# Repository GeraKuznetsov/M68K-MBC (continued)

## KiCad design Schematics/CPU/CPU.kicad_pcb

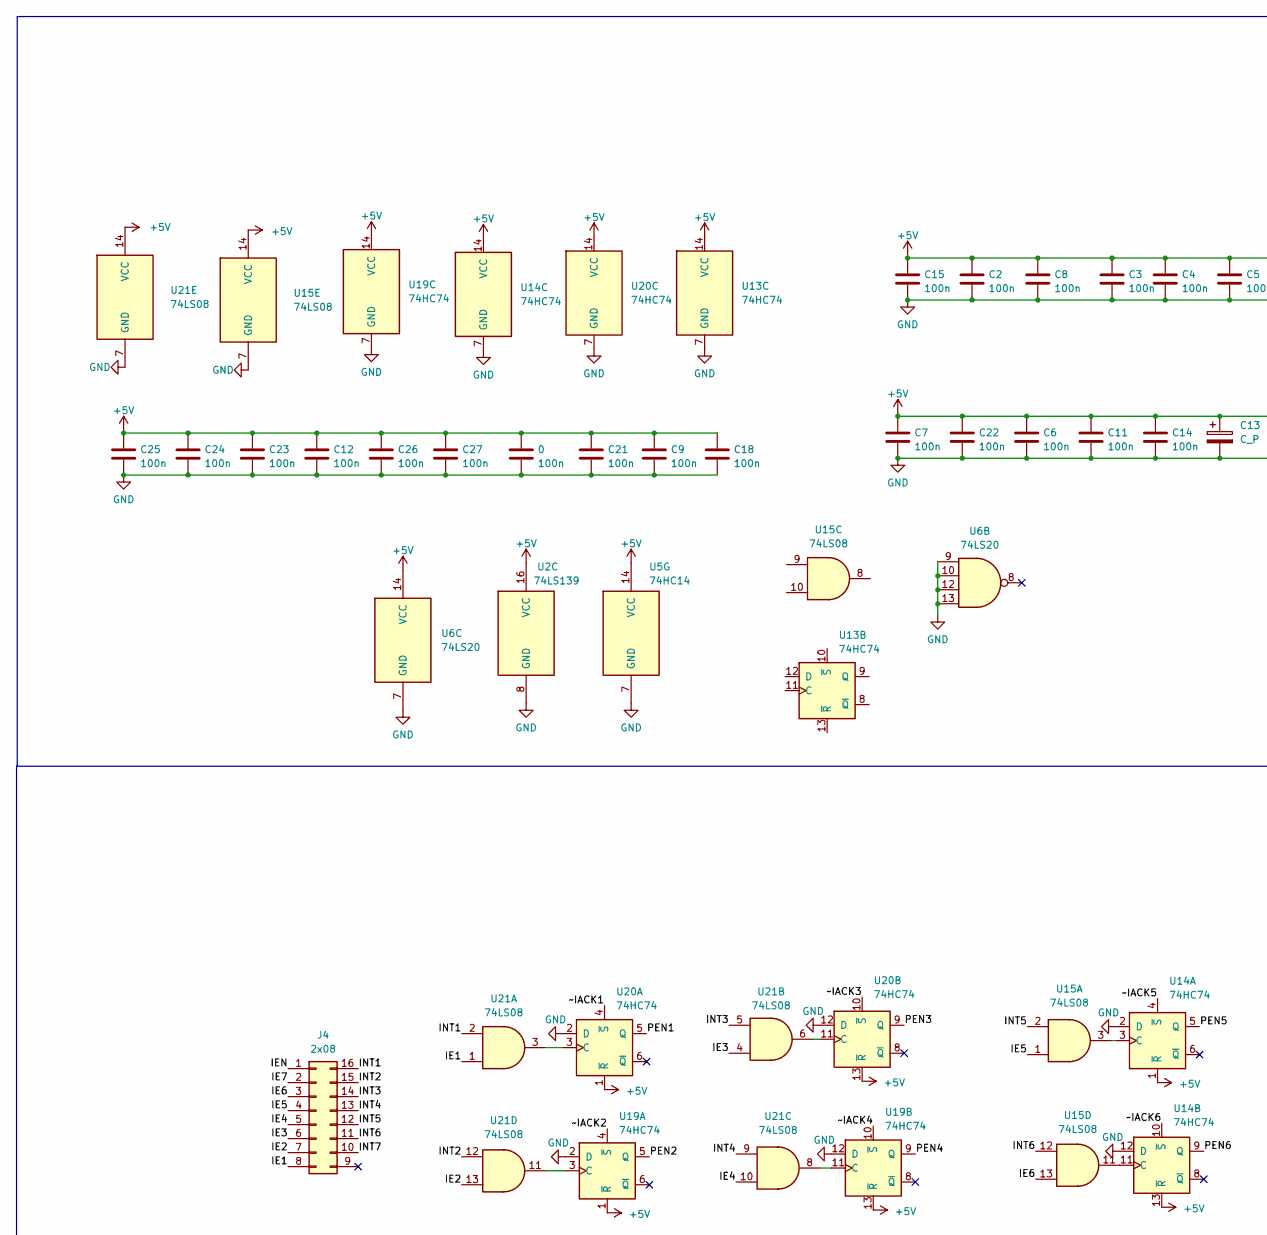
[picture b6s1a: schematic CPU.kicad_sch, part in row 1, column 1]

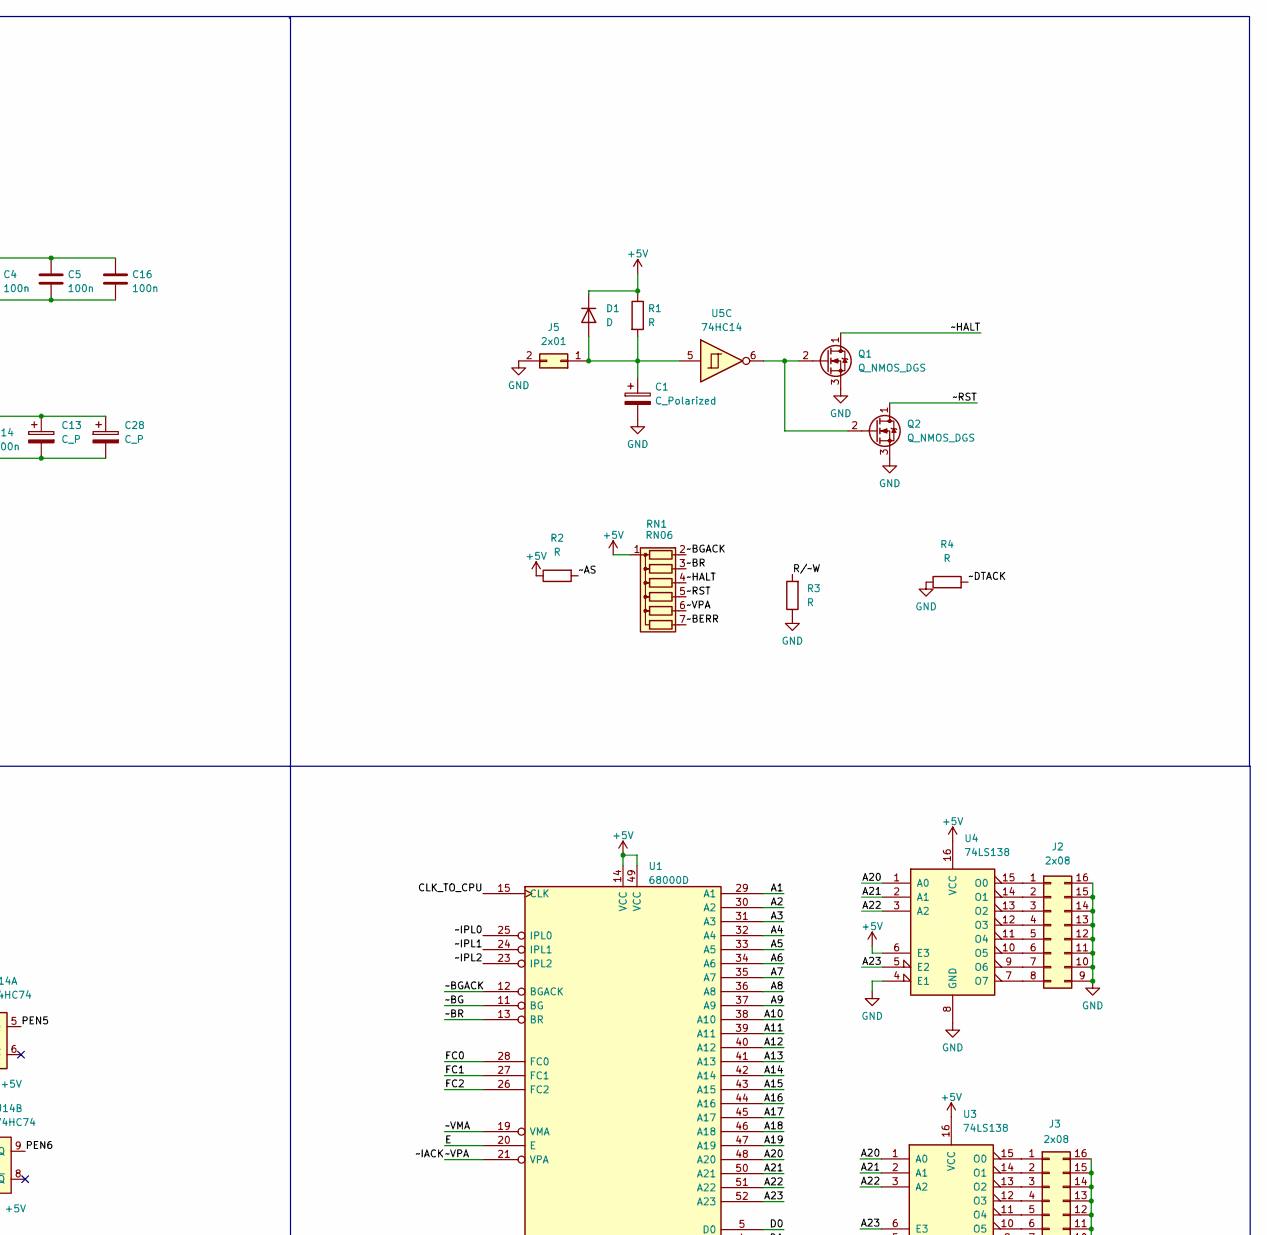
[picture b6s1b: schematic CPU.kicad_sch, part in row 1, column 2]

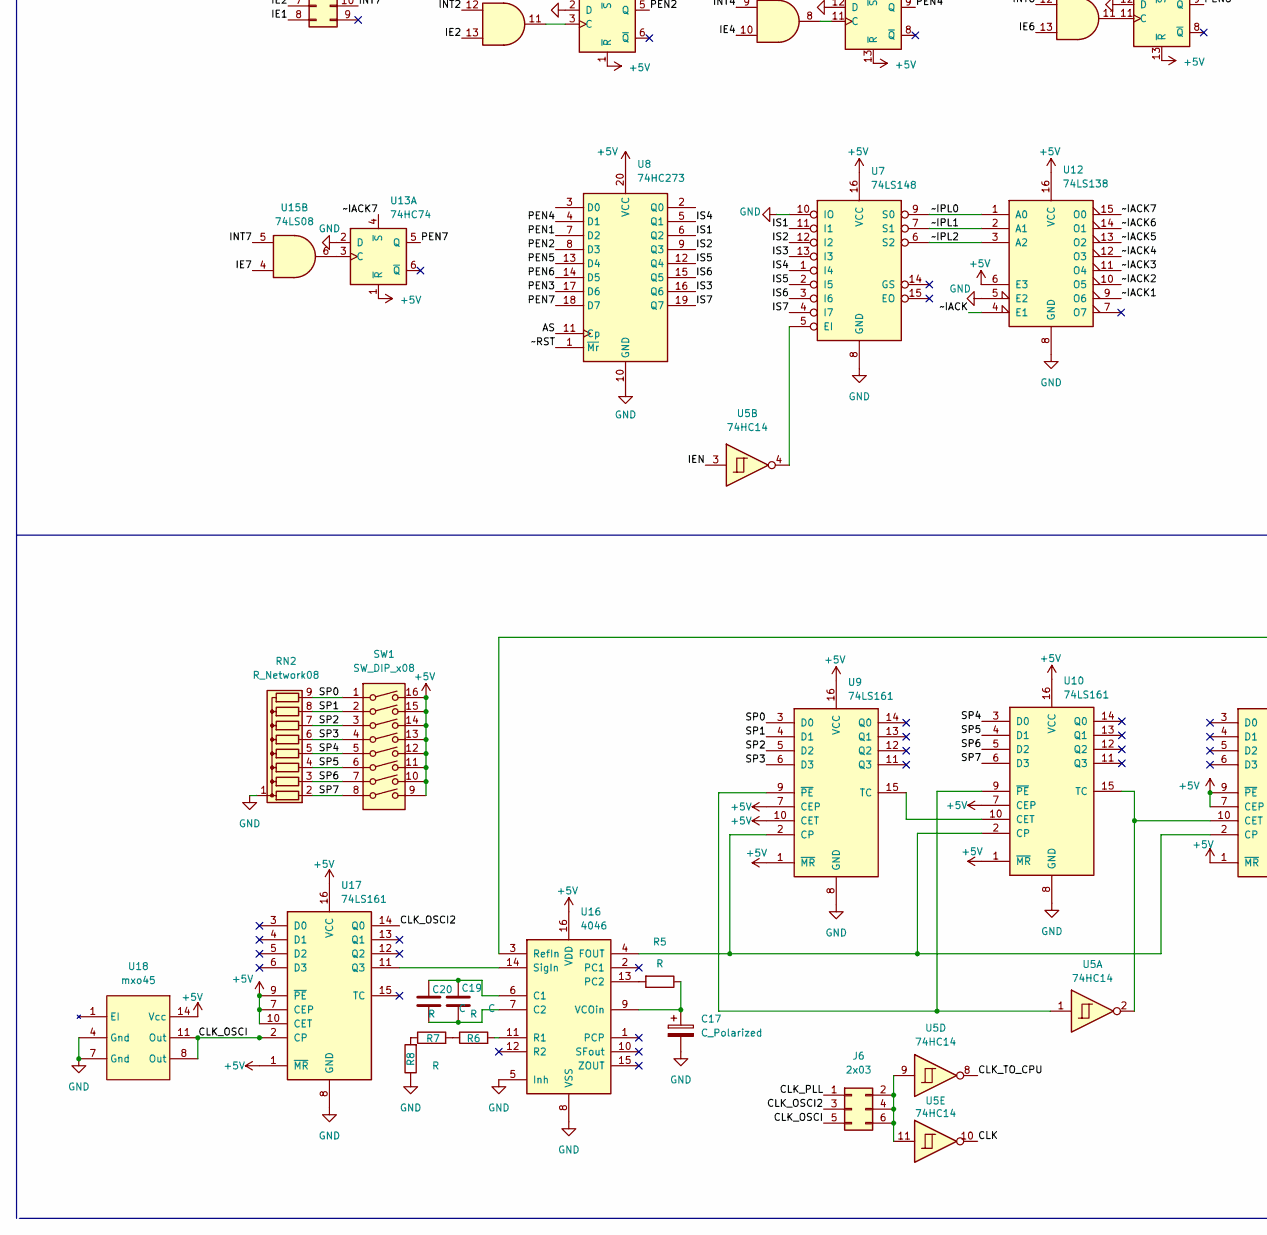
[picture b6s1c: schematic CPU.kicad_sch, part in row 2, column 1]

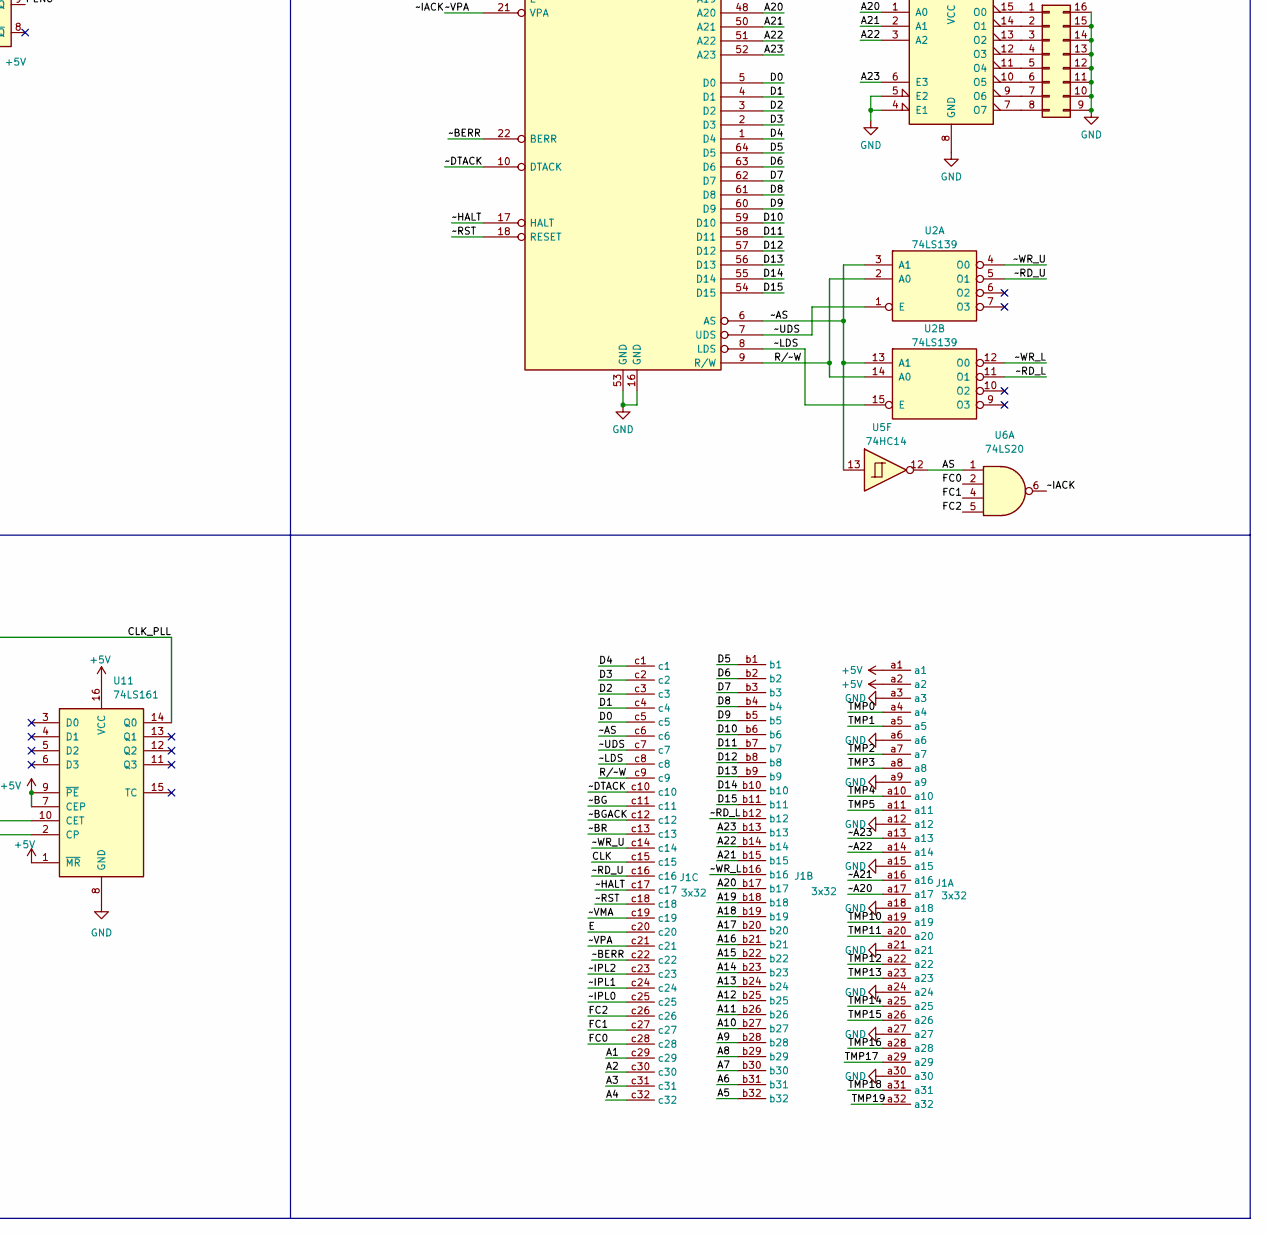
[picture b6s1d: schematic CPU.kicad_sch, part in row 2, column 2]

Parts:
0: 100n; DIP-2_200_ELL
C1, C17: C_Polarized; CP_Radial_D4.0mm_P1.50mm
C2, C3, C4, C5, C6, C7, C8, C9, C11, C12, C14, C15, C16, C18, C21, C22, C23, C24, C25, C26, C27: 100n; DIP-2_200_ELL
C13, C28: C_P; CP_Radial_D4.0mm_P1.50mm
C19, C20: C; DIP-2_200_ELL
D1: D; D_DO-35_SOD27_P7.62mm_Horizontal
J1: 3x32; DIN41612_R_3x32_Male_Horizontal_THT
J2, J3, J4: 2x08; 2x08 finger
J5: 2x01; 2x01 finger
J6: 2x03; PinHeader_2x03_P2.54mm_Vertical
Q1, Q2: Q_NMOS_DGS; TO-92
R1, R2, R3, R4: R; res
R5, R6, R7, R8: R; R_Axial_DIN0411_L9.9mm_D3.6mm_P5.08mm_Vertical
RN1: RN06; R_Array_SIP7
RN2: R_Network08; R_Array_SIP9
SW1: SW_DIP_x08; DIP-16
U1: 68000D; DIP-64_875_ELL
U2: 74LS139; DIP-16
U3, U4, U12: 74LS138; DIP-16
U5: 74HC14; DIP-14
U6: 74LS20; DIP-14
U7: 74LS148; DIP-16
U8: 74HC273; DIP-20
U9, U10, U11, U17: 74LS161; DIP-16
U13, U14, U19, U20: 74HC74; DIP-14
U15, U21: 74LS08; DIP-14
U16: 4046; DIP-16
U18: mxo45

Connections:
+5V: 0.1, C2.1, C3.1, C4.1, C5.1, C6.1, C7.1, C8.1, C9.1, C11.1, C12.1, C13.1, C14.1, C15.1, C16.1, C18.1, C21.1, C22.1, C23.1, C24.1, C25.1, C26.1, C27.1, C28.1, D1.1 (K), J1.a1, J1.a2, R1.1, R2.1, RN1.1 (common), SW1.9, SW1.10, SW1.11, SW1.12, SW1.13, SW1.14, SW1.15, SW1.16, U1.14 (VCC), U1.49 (VCC), U2.16 (VCC), U3.16 (VCC), U4.6 (E3), U4.16 (VCC), U5.14 (VCC), U6.14 (VCC), U7.16 (VCC), U8.20 (VCC), U9.1 (~MR), U9.7 (CEP), U9.10 (CET), U9.16 (VCC), U10.1 (~MR), U10.7 (CEP), U10.16 (VCC), U11.1 (~MR), U11.7 (CEP), U11.9 (~PE), U11.16 (VCC), U12.6 (E3), U12.16 (VCC), U13.1 (~R), U13.14 (VCC), U14.1 (~R), U14.13 (~R), U14.14 (VCC), U15.14 (VCC), U16.16 (VDD), U17.1 (~MR), U17.7 (CEP), U17.9 (~PE), U17.10 (CET), U17.16 (VCC), U18.14 (Vcc), U19.1 (~R), U19.13 (~R), U19.14 (VCC), U20.1 (~R), U20.13 (~R), U20.14 (VCC), U21.14 (VCC)
/A1: J1.c29, U1.29 (A1)
/A2: J1.c30, U1.30 (A2)
/A3: J1.c31, U1.31 (A3)
/A4: J1.c32, U1.32 (A4)
/A5: J1.b32, U1.33 (A5)
/A6: J1.b31, U1.34 (A6)
/A7: J1.b30, U1.35 (A7)
/A8: J1.b29, U1.36 (A8)
/A9: J1.b28, U1.37 (A9)
/A10: J1.b27, U1.38 (A10)
/A11: J1.b26, U1.39 (A11)
/A12: J1.b25, U1.40 (A12)
/A13: J1.b24, U1.41 (A13)
/A14: J1.b23, U1.42 (A14)
/A15: J1.b22, U1.43 (A15)
/A16: J1.b21, U1.44 (A16)
/A17: J1.b20, U1.45 (A17)
/A18: J1.b19, U1.46 (A18)
/A19: J1.b18, U1.47 (A19)
/A20: J1.b17, U1.48 (A20), U3.1 (A0), U4.1 (A0)
/A21: J1.b15, U1.50 (A21), U3.2 (A1), U4.2 (A1)
/A22: J1.b14, U1.51 (A22), U3.3 (A2), U4.3 (A2)
/A23: J1.b13, U1.52 (A23), U3.6 (E3), U4.5 (E2)
/AS: U5.12, U6.1, U8.11 (Cp)
/CLK: J1.c15, U5.10
/CLK_OSCI: J6.5, U17.2 (CP), U18.8 (Out), U18.11 (Out)
/CLK_OSCI2: J6.3, U17.14 (Q0)
/CLK_PLL: J6.1, U11.14 (Q0), U16.3 (RefIn)
/CLK_TO_CPU: U1.15 (CLK), U5.8
/D0: J1.c5, U1.5 (D0)
/D1: J1.c4, U1.4 (D1)
/D2: J1.c3, U1.3 (D2)
/D3: J1.c2, U1.2 (D3)
/D4: J1.c1, U1.1 (D4)
/D5: J1.b1, U1.64 (D5)
/D6: J1.b2, U1.63 (D6)
/D7: J1.b3, U1.62 (D7)
/D8: J1.b4, U1.61 (D8)
/D9: J1.b5, U1.60 (D9)
/D10: J1.b6, U1.59 (D10)
/D11: J1.b7, U1.58 (D11)
/D12: J1.b8, U1.57 (D12)
/D13: J1.b9, U1.56 (D13)
/D14: J1.b10, U1.55 (D14)
/D15: J1.b11, U1.54 (D15)
/E: J1.c20, U1.20 (E)
/FC0: J1.c28, U1.28 (FC0), U6.2
/FC1: J1.c27, U1.27 (FC1), U6.4
/FC2: J1.c26, U1.26 (FC2), U6.5
/IE1: J4.8, U21.1
/IE2: J4.7, U21.13
/IE3: J4.6, U21.4
/IE4: J4.5, U21.10
/IE5: J4.4, U15.1
/IE6: J4.3, U15.13
/IE7: J4.2, U15.4
/IEN: J4.1, U5.3
/INT1: J4.16, U21.2
/INT2: J4.15, U21.12
/INT3: J4.14, U21.5
/INT4: J4.13, U21.9
/INT5: J4.12, U15.2
/INT6: J4.11, U15.12
/INT7: J4.10, U15.5
/IS1: U7.11 (I1), U8.6 (Q2)
/IS2: U7.12 (I2), U8.9 (Q3)
/IS3: U7.13 (I3), U8.16 (Q6)
/IS4: U7.1 (I4), U8.5 (Q1)
/IS5: U7.2 (I5), U8.12 (Q4)
/IS6: U7.3 (I6), U8.15 (Q5)
/IS7: U7.4 (I7), U8.19 (Q7)
/PEN1: U8.7 (D2), U20.5 (Q)
/PEN2: U8.8 (D3), U19.5 (Q)
/PEN3: U8.17 (D6), U20.9 (Q)
/PEN4: U8.4 (D1), U19.9 (Q)
/PEN5: U8.13 (D4), U14.5 (Q)
/PEN6: U8.14 (D5), U14.9 (Q)
/PEN7: U8.18 (D7), U13.5 (Q)
/R/~W: J1.c9, R3.2, U1.9 (R/W), U2.2 (A0), U2.14 (A0)
/SP0: RN2.9 (R8), SW1.1, U9.3 (D0)
/SP1: RN2.8 (R7), SW1.2, U9.4 (D1)
/SP2: RN2.7 (R6), SW1.3, U9.5 (D2)
/SP3: RN2.6 (R5), SW1.4, U9.6 (D3)
/SP4: RN2.5 (R4), SW1.5, U10.3 (D0)
/SP5: RN2.4 (R3), SW1.6, U10.4 (D1)
/SP6: RN2.3 (R2), SW1.7, U10.5 (D2)
/SP7: RN2.2 (R1), SW1.8, U10.6 (D3)
/TMP0: J1.a4
/TMP1: J1.a5
/TMP2: J1.a7
/TMP3: J1.a8
/TMP4: J1.a10
/TMP5: J1.a11
/TMP10: J1.a19
/TMP11: J1.a20
/TMP12: J1.a22
/TMP13: J1.a23
/TMP14: J1.a25
/TMP15: J1.a26
/TMP16: J1.a28
/TMP17: J1.a29
/TMP18: J1.a31
/TMP19: J1.a32
/~A20: J1.a17
/~A21: J1.a16
/~A22: J1.a14
/~A23: J1.a13
/~AS: J1.c6, R2.2, U1.6 (AS), U2.3 (A1), U2.13 (A1), U5.13
/~BERR: J1.c22, RN1.7 (R6), U1.22 (BERR)
/~BG: J1.c11, U1.11 (BG)
/~BGACK: J1.c12, RN1.2 (R1), U1.12 (BGACK)
/~BR: J1.c13, RN1.3 (R2), U1.13 (BR)
/~DTACK: J1.c10, R4.2, U1.10 (DTACK)
/~HALT: J1.c17, Q1.1 (D), RN1.4 (R3), U1.17 (HALT)
/~IACK: J1.c21, RN1.6 (R5), U1.21 (VPA), U6.6, U12.4 (E1)
/~IACK1: U12.9 (O6), U20.4 (~S)
/~IACK2: U12.10 (O5), U19.4 (~S)
/~IACK3: U12.11 (O4), U20.10 (~S)
/~IACK4: U12.12 (O3), U19.10 (~S)
/~IACK5: U12.13 (O2), U14.4 (~S)
/~IACK6: U12.14 (O1), U14.10 (~S)
/~IACK7: U12.15 (O0), U13.4 (~S)
/~IPL0: J1.c25, U1.25 (IPL0), U7.9 (S0), U12.1 (A0)
/~IPL1: J1.c24, U1.24 (IPL1), U7.7 (S1), U12.2 (A1)
/~IPL2: J1.c23, U1.23 (IPL2), U7.6 (S2), U12.3 (A2)
/~LDS: J1.c8, U1.8 (LDS), U2.15 (E)
/~RD_L: J1.b12, U2.11 (O1)
/~RD_U: J1.c16, U2.5 (O1)
/~RST: J1.c18, Q2.1 (D), RN1.5 (R4), U1.18 (RESET), U8.1 (~Mr)
/~UDS: J1.c7, U1.7 (UDS), U2.1 (E)
/~VMA: J1.c19, U1.19 (VMA)
/~WR_L: J1.b16, U2.12 (O0)
/~WR_U: J1.c14, U2.4 (O0)
GND: 0.2, C1.2, C2.2, C3.2, C4.2, C5.2, C6.2, C7.2, C8.2, C9.2, C11.2, C12.2, C13.2, C14.2, C15.2, C16.2, C17.2, C18.2, C21.2, C22.2, C23.2, C24.2, C25.2, C26.2, C27.2, C28.2, J1.a3, J1.a6, J1.a9, J1.a12, J1.a15, J1.a18, J1.a21, J1.a24, J1.a27, J1.a30, J2.9, J2.10, J2.11, J2.12, J2.13, J2.14, J2.15, J2.16, J3.9, J3.10, J3.11, J3.12, J3.13, J3.14, J3.15, J3.16, J5.2, Q1.3 (S), Q2.3 (S), R3.1, R4.1, R8.1, RN2.1 (common), U1.16 (GND), U1.53 (GND), U2.8 (GND), U3.4 (E1), U3.5 (E2), U3.8 (GND), U4.4 (E1), U4.8 (GND), U5.7 (GND), U6.7 (GND), U6.9, U6.10, U6.12, U6.13, U7.8 (GND), U7.10 (IO), U8.10 (GND), U9.8 (GND), U10.8 (GND), U11.8 (GND), U12.5 (E2), U12.8 (GND), U13.2 (D), U13.7 (GND), U14.2 (D), U14.7 (GND), U14.12 (D), U15.7 (GND), U16.5 (Inh), U16.8 (VSS), U17.8 (GND), U18.4 (Gnd), U18.7 (Gnd), U19.2 (D), U19.7 (GND), U19.12 (D), U20.2 (D), U20.7 (GND), U20.12 (D), U21.7 (GND)
unnamed: C1.1, D1.2 (A), J5.1, R1.2, U5.5
unnamed: C17.1, R5.1, U16.9 (VCOin)
unnamed: C19.1, C20.1, U16.6 (C1)
unnamed: C19.2, C20.2, U16.7 (C2)
unnamed: J2.1, U4.15 (O0)
unnamed: J2.2, U4.14 (O1)
unnamed: J2.3, U4.13 (O2)
unnamed: J2.4, U4.12 (O3)
unnamed: J2.5, U4.11 (O4)
unnamed: J2.6, U4.10 (O5)
unnamed: J2.7, U4.9 (O6)
unnamed: J2.8, U4.7 (O7)
unnamed: J3.1, U3.15 (O0)
unnamed: J3.2, U3.14 (O1)
unnamed: J3.3, U3.13 (O2)
unnamed: J3.4, U3.12 (O3)
unnamed: J3.5, U3.11 (O4)
unnamed: J3.6, U3.10 (O5)
unnamed: J3.7, U3.9 (O6)
unnamed: J3.8, U3.7 (O7)
unnamed: J6.2, J6.4, J6.6, U5.9, U5.11
unnamed: Q1.2 (G), Q2.2 (G), U5.6
unnamed: R5.2, U16.13 (PC2)
unnamed: R6.1, R7.2
unnamed: R6.2, U16.11 (R1)
unnamed: R7.1, R8.2
unnamed: U5.4, U7.5 (EI)
unnamed: U9.2 (CP), U10.2 (CP), U11.2 (CP), U16.4 (FOUT)
unnamed: U5.1, U9.9 (~PE), U10.9 (~PE)
unnamed: U9.15 (TC), U10.10 (CET)
unnamed: U5.2, U10.15 (TC), U11.10 (CET)
unnamed: U13.3 (C), U15.6
unnamed: U14.3 (C), U15.3
unnamed: U14.11 (C), U15.11
unnamed: U16.14 (SigIn), U17.11 (Q3)
unnamed: U19.3 (C), U21.11
unnamed: U19.11 (C), U21.8
unnamed: U20.3 (C), U21.3
unnamed: U20.11 (C), U21.6

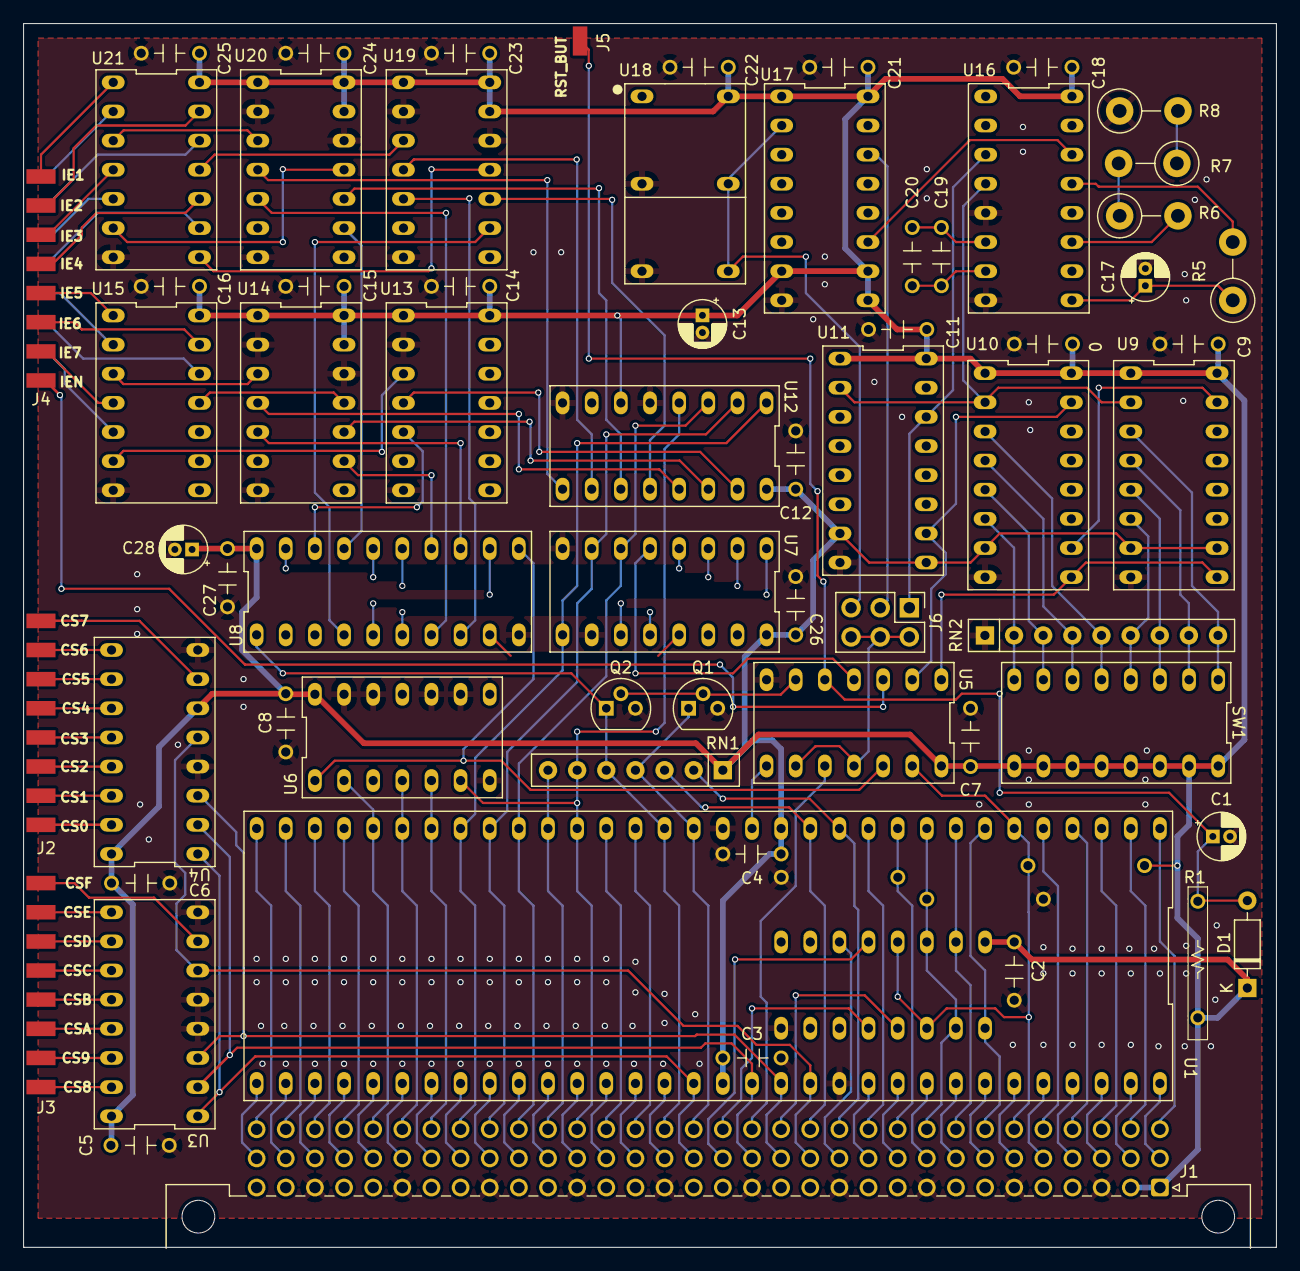
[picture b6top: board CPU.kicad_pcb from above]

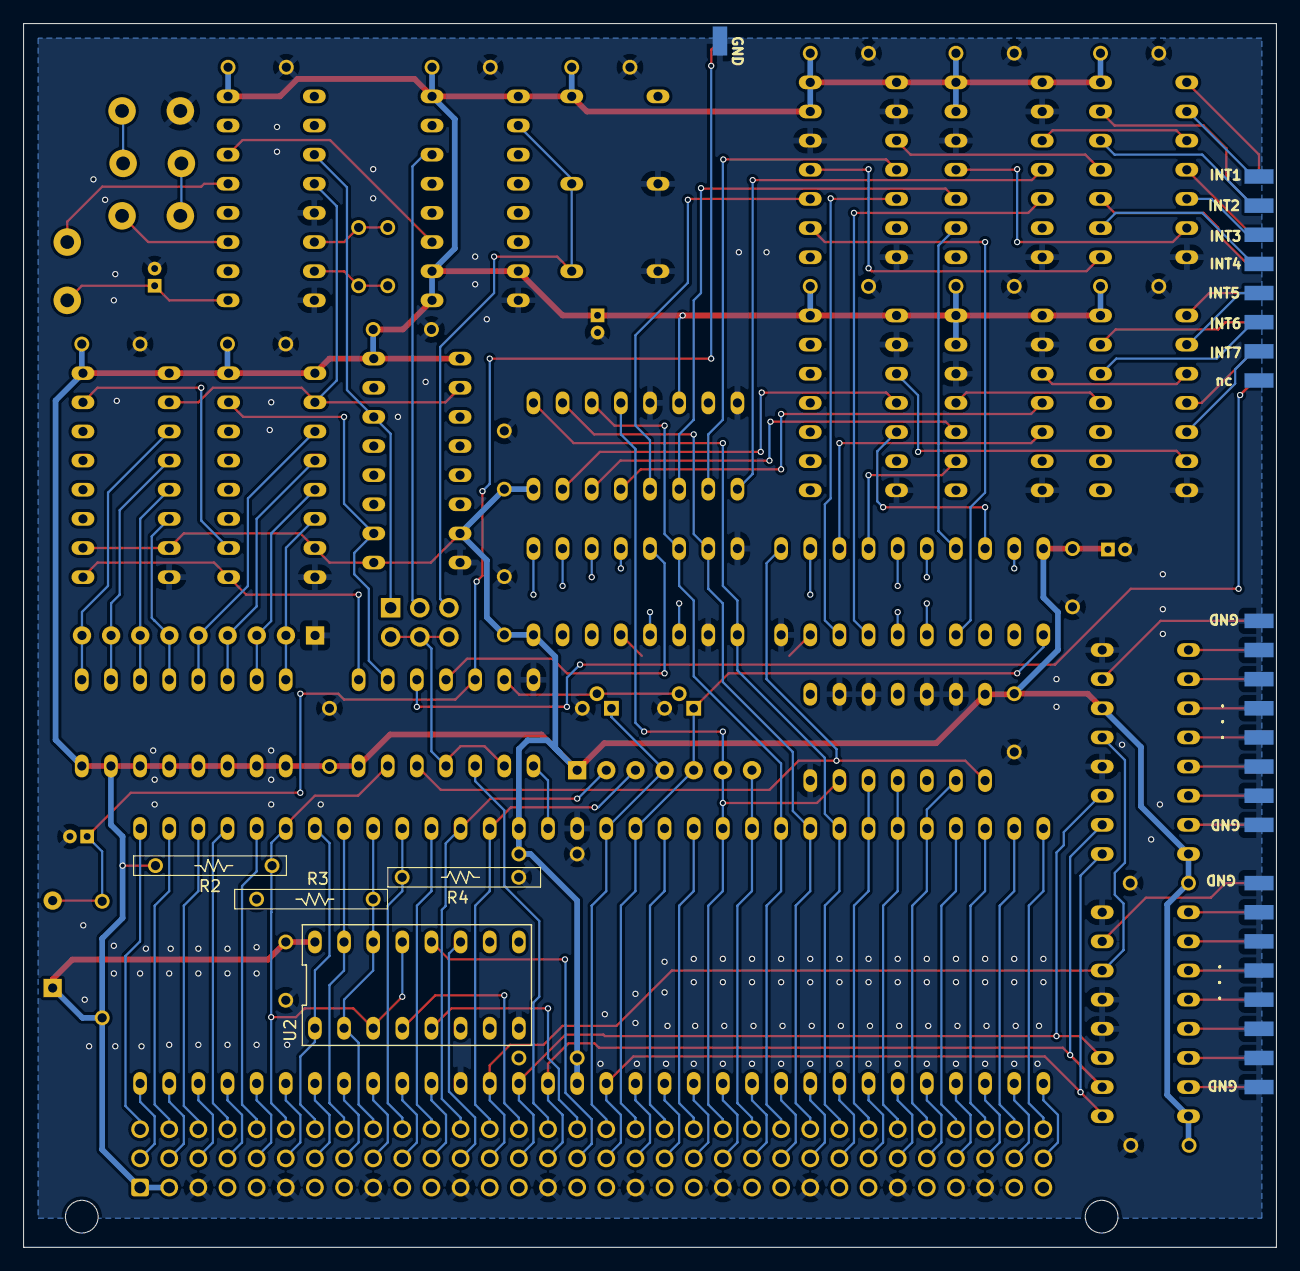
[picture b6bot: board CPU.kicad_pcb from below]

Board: 2 copper layers, 109.2 x 106.7 mm, 69 parts (4 on the bottom side), 154 nets.

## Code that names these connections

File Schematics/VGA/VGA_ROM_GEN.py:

import struct

file = "out.bin"
output = open(file, "wb")

HSYNC = 1 #NEG
VSYNC = 2 #NEG
RESX = 4  #NEG
RESY = 8  #NEG
INCY = 16 
VIS = 32  #NEG

NEGATE = HSYNC | VSYNC | VIS | RESX | RESY

H_VIS = 640 / 16
H_FP = 16 / 16
H_SYNC = 96 / 16
H_BP = 48 / 16 

Y_VIS = 480
Y_FP = 10
Y_SYNC = 2
Y_BP = 33

for y in range(1024):
	for x in range(64):
		b = 0
		if x < H_VIS and y < Y_VIS:
			b |= VIS
			
		if x >= H_VIS + H_FP and x < H_VIS + H_FP + H_SYNC:
			b |= HSYNC
		if x == H_VIS + H_FP + H_SYNC + H_BP - 2:
			b |= INCY
		if x >= H_VIS + H_FP + H_SYNC + H_BP - 1:
			b |= RESX
			if y == Y_VIS + Y_FP + Y_SYNC + Y_BP - 1:
				b |= RESY
			else:
				b |= INCY
			
		if y >= Y_VIS + Y_FP and y < Y_VIS + Y_FP + Y_SYNC:
			b |= VSYNC
			
		b ^= NEGATE
		output.write(struct.pack('1B', b))
		output.write(struct.pack('1B', b))
		
H_VIS = (640 / 16) - 8
H_FP = (16 / 16) + 4
H_SYNC = (96 / 16)
H_BP = (48 / 16) + 4
		
Y_VIS = 480 / 2
		
for y in range(1024):
	for x in range(64):
		b = 0
		if x < H_VIS and y < Y_VIS:
			b |= VIS
			
		if x >= H_VIS + H_FP and x < H_VIS + H_FP + H_SYNC:
			b |= HSYNC
			
		if x == H_VIS + H_FP + H_SYNC + H_BP - 2 and y >= Y_VIS:
			b |= INCY
			
		if x >= H_VIS + H_FP + H_SYNC + H_BP - 1:
			b |= RESX
			if y == Y_VIS + Y_FP + Y_SYNC + Y_BP - 1:
				b |= RESY
			else:
				b |= INCY
			
		if ((y == Y_VIS + Y_FP - 1 and x >= 50-4) or (y == Y_VIS + Y_FP) or (y == Y_VIS + Y_FP + 1 and x < 4)):
			b |= VSYNC
			
		b ^= NEGATE
		output.write(struct.pack('1B', b))
		output.write(struct.pack('1B', b))
		
print("done")

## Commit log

2022-12-12 init
2023-07-18 7/18/2023
